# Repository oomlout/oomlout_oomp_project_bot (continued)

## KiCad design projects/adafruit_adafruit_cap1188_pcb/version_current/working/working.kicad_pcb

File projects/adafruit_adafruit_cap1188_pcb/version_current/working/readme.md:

# Adafruit-CAP1188-PCB by adafruit  
This is a harvested standardized copy of a project from github.  
The original project can be found at:  
https://github.com/adafruit/Adafruit-CAP1188-PCB  
Please consult that link for additional, details, files, and license information.  
Note: It was auto harvested and if the original repo had more than one board file or anything out of the ordinary the files here are likely not representative.

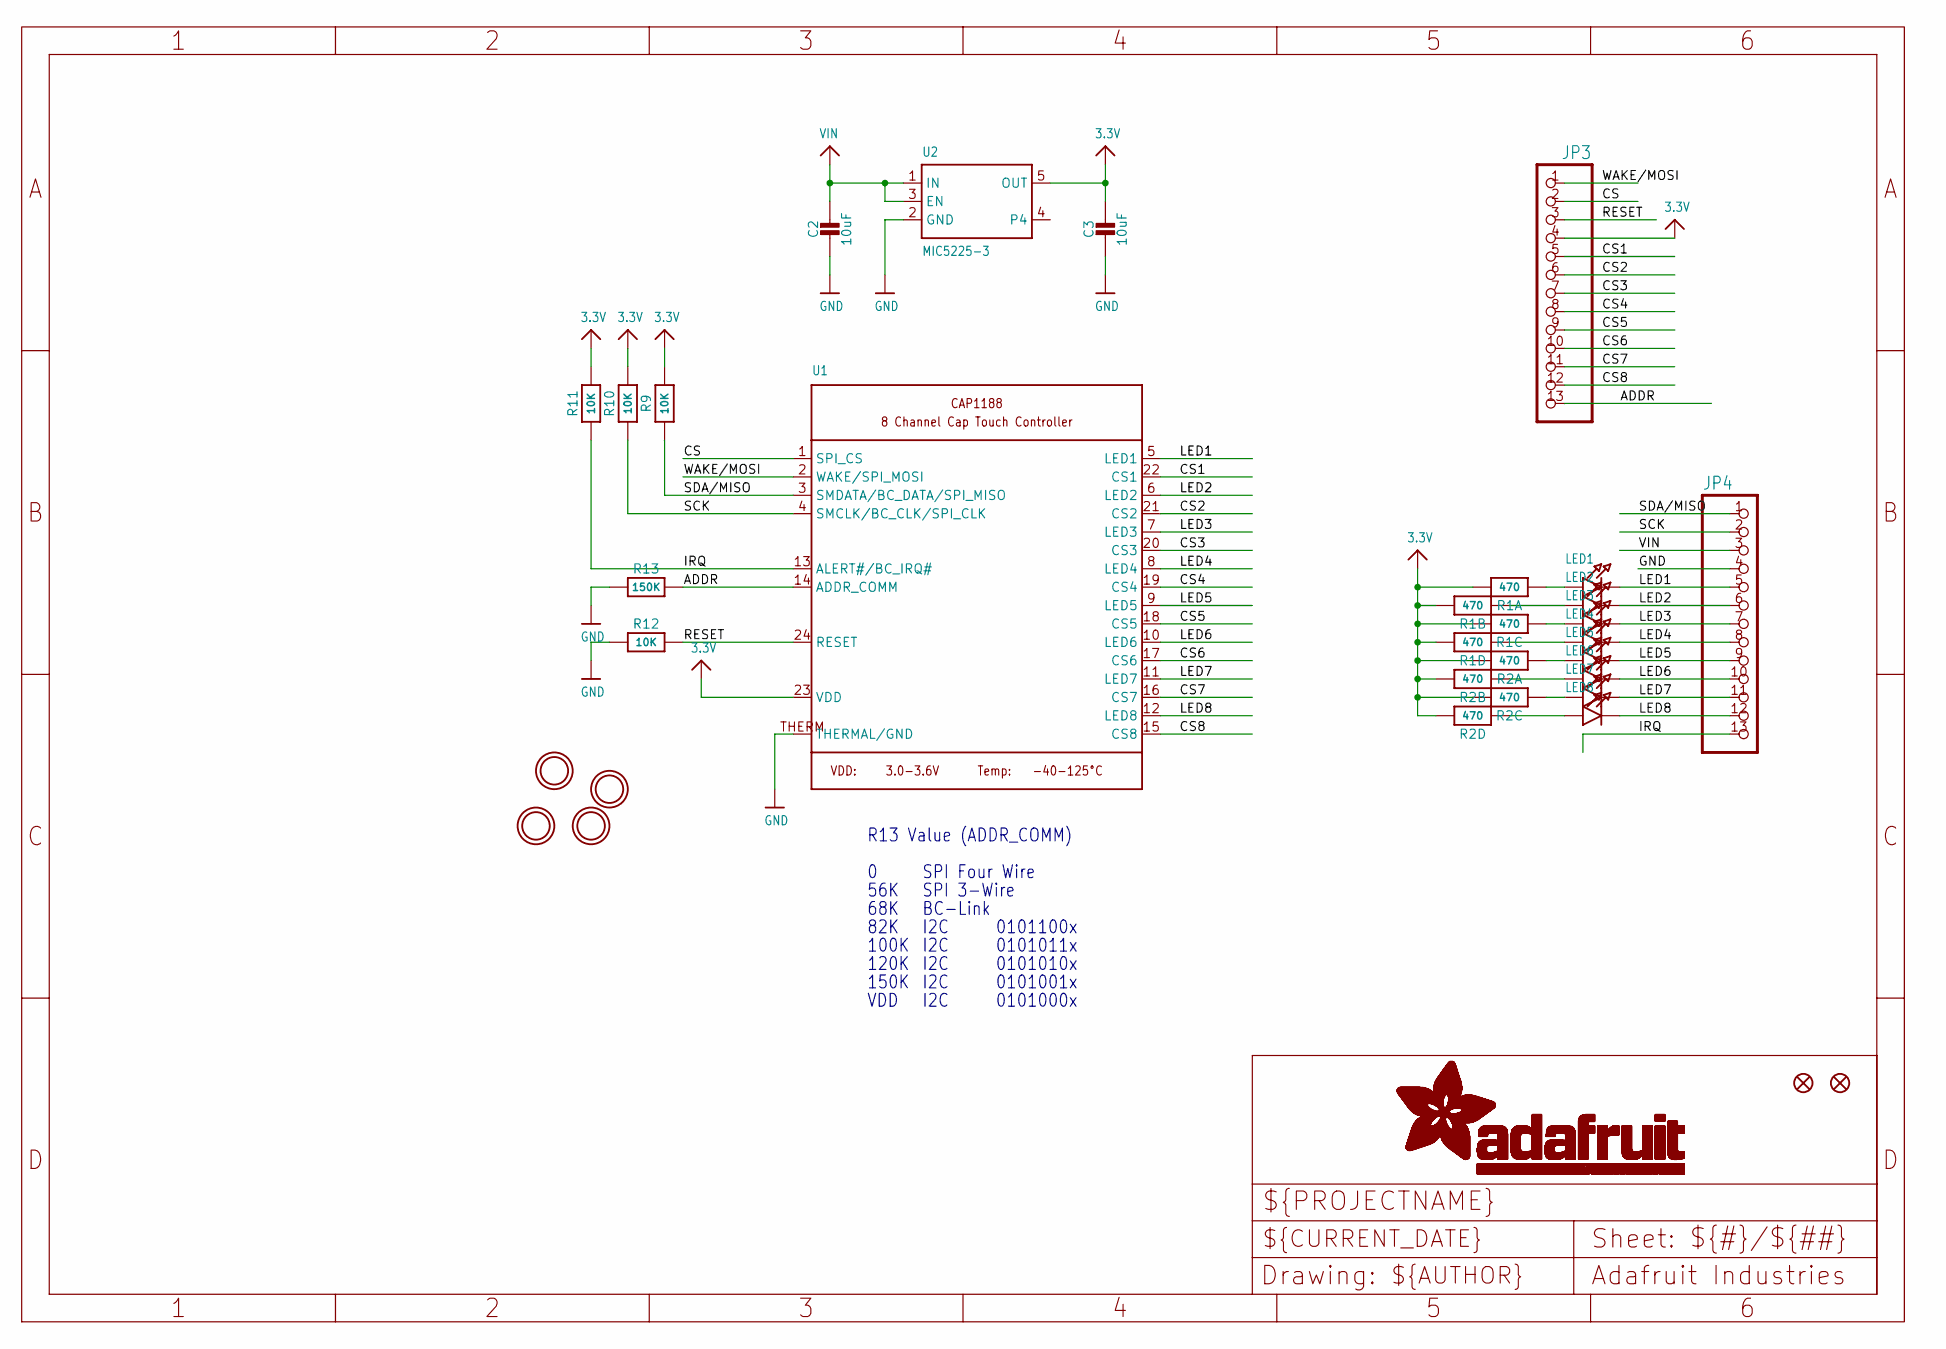
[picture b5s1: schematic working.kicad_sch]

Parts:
C2, C3: 10uF; 0805-NO
FID1, FID2: FIDUCIAL""; FIDUCIAL_1MM
JP3, JP4: HEADER-1X13; 1X13_ROUND_70
LED1, LED2, LED3, LED4, LED5, LED6, LED7, LED8: LED0805; CHIPLED_0805
R1, R2: 470; RESPACK_4X0603
R9, R10, R11, R12: 10K; 0805-NO
R13: 150K; _0805MP
U1: CAP1188; QFN24_4MM_SMSC
U2: MIC5225-3; SOT23-5
U$7, U$8, U$9, U$10: MOUNTINGHOLE2.0; MOUNTINGHOLE_2.0_PLATED

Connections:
3.3V: C3.1, JP3.4, R1.5 (2), R1.6 (2), R1.7 (2), R1.8 (2), R2.5 (2), R2.6 (2), R2.7 (2), R2.8 (2), R9.2, R10.2, R11.2, U1.23 (VDD), U2.5 (OUT)
ADDR: JP3.13, R13.2, U1.14 (ADDR_COMM)
CS: JP3.2, U1.1 (SPI_CS)
CS1: JP3.5, U1.22 (CS1)
CS2: JP3.6, U1.21 (CS2)
CS3: JP3.7, U1.20 (CS3)
CS4: JP3.8, U1.19 (CS4)
CS5: JP3.9, U1.18 (CS5)
CS6: JP3.10, U1.17 (CS6)
CS7: JP3.11, U1.16 (CS7)
CS8: JP3.12, U1.15 (CS8)
GND: C2.2, C3.2, JP4.4, R12.1, R13.1, U1.THERM (THERMAL/GND), U2.2 (GND)
IRQ: JP4.13, R11.1, U1.13 (ALERT#/BC_IRQ#)
LED1: JP4.5, LED1.C, U1.5 (LED1)
LED2: JP4.6, LED2.C, U1.6 (LED2)
LED3: JP4.7, LED3.C, U1.7 (LED3)
LED4: JP4.8, LED4.C, U1.8 (LED4)
LED5: JP4.9, LED5.C, U1.9 (LED5)
LED6: JP4.10, LED6.C, U1.10 (LED6)
LED7: JP4.11, LED7.C, U1.11 (LED7)
LED8: JP4.12, LED8.C, U1.12 (LED8)
unnamed: LED1.A, R1.1
unnamed: LED2.A, R1.2 (1)
unnamed: LED3.A, R1.3 (1)
unnamed: LED4.A, R1.4 (1)
unnamed: LED5.A, R2.1
unnamed: LED6.A, R2.2 (1)
unnamed: LED7.A, R2.3 (1)
unnamed: LED8.A, R2.4 (1)
RESET: JP3.3, R12.2, U1.24 (RESET)
SCK: JP4.2, R10.1, U1.4 (SMCLK/BC_CLK/SPI_CLK)
SDA/MISO: JP4.1, R9.1, U1.3 (SMDATA/BC_DATA/SPI_MISO)
VIN: C2.1, JP4.3, U2.1 (IN), U2.3 (EN)
WAKE/MOSI: JP3.1, U1.2 (WAKE/SPI_MOSI)

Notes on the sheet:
0101001x
68K
0101010x
150K
0101011x
VDD
I2C
0101000x
120K
0101100x
82K
56K
SPI 3-Wire
100K
R13 Value (ADDR_COMM)
SPI Four Wire
BC-Link

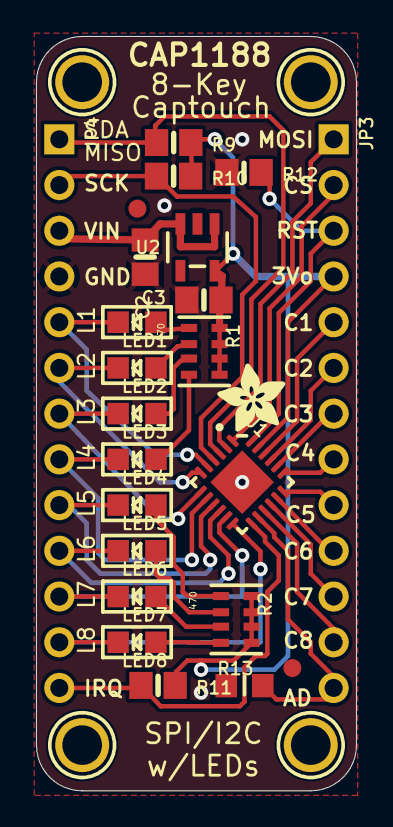
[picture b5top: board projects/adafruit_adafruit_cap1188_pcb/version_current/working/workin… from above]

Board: 2 copper layers, 17.8 x 41.9 mm, 29 parts (1 on the bottom side), 34 nets.

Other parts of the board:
U$13: ADAFRUIT_3.5MM
U$14: ADAFRUIT_9MM

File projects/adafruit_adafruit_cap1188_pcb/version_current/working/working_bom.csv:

Row,Description,Part,References,Value,Footprint,Quantity Per PCB,Status,Datasheet
1,,CAP_CERAMIC0805-NOOUTLINE,C2 C3,10uF,0805-NO,2, ,
2,,HEADER-1X13,JP3 JP4,HEADER-1X13,1X13_ROUND_70,2, ,
3,,LED0805,LED1 LED2 LED3 LED4 LED5 LED6 LED7 LED8,LED0805,CHIPLED_0805,8, ,
4,,RESISTOR_4PACK,R1 R2,470,RESPACK_4X0603,2, ,
5,,RESISTOR0805_NOOUTLINE,R9 R10 R11 R12,10K,0805-NO,4, ,
6,,RESISTOR_0805MP,R13,150K,_0805MP,1, ,
7,,CAP1188,U1,CAP1188,QFN24_4MM_SMSC,1, ,
8,,VREG_SOT23-5,U2,MIC5225-3,SOT23-5,1, ,





Project info:
Schematic:,working
Variant:,default
Revision:,
Date:,2023-08-02_17-08-32
KiCad Version:,7.0.6-7.0.6~ubuntu22.04.1
Statistics:
Component Groups:,8
Component Count:,21 (0 SMD/ 0 THT)
Fitted Components:,21 (0 SMD/ 0 THT)
Number of PCBs:,1
Total Components:,21

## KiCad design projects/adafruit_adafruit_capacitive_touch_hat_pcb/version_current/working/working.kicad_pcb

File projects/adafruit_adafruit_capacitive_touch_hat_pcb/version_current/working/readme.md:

# Adafruit-Capacitive-Touch-HAT-PCB by adafruit  
This is a harvested standardized copy of a project from github.  
The original project can be found at:  
https://github.com/adafruit/Adafruit-Capacitive-Touch-HAT-PCB  
Please consult that link for additional, details, files, and license information.  
Note: It was auto harvested and if the original repo had more than one board file or anything out of the ordinary the files here are likely not representative.

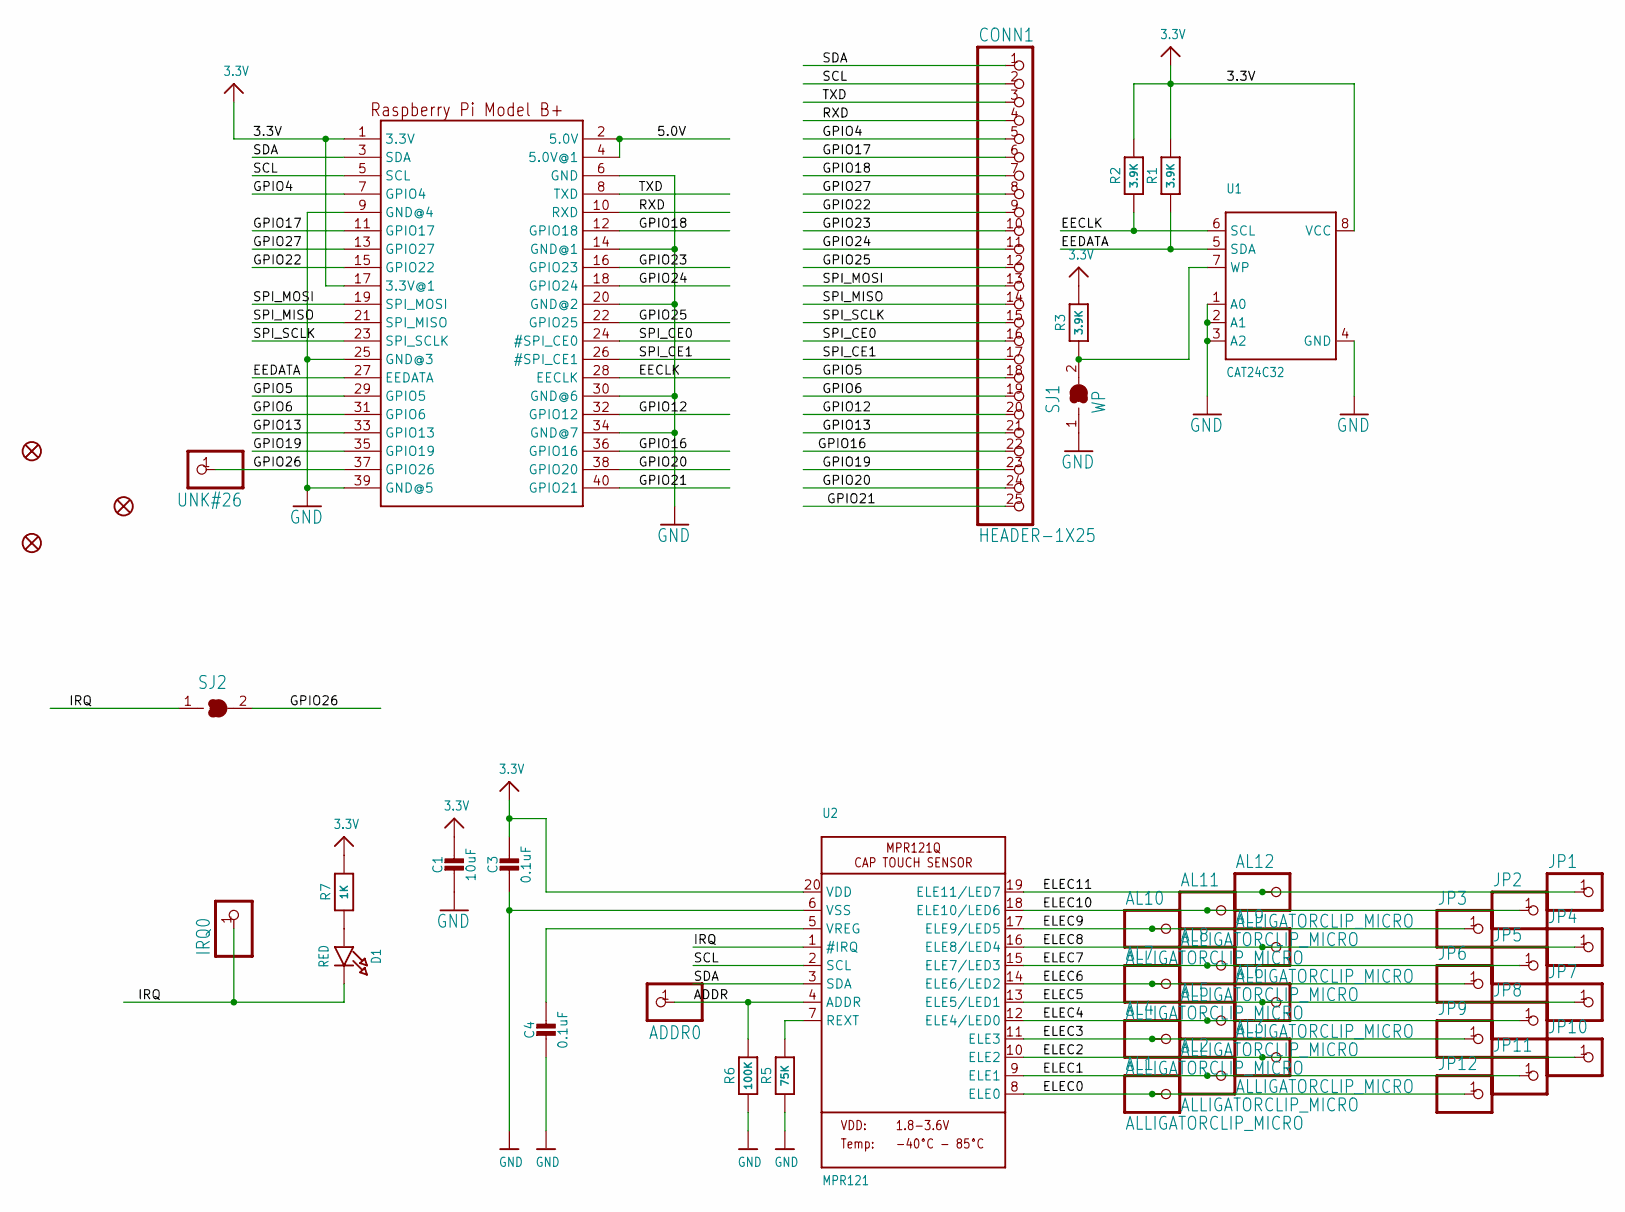
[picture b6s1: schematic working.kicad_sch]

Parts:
ADDR0: HEADER-1X1ROUND; 1X01_ROUND
AL1, AL2, AL3, AL4, AL5, AL6, AL7, AL8, AL9, AL10, AL11, AL12: ALLIGATORCLIP_MICRO; ALLIGATORCLIP
C1: 10uF; 0805-NO
C3, C4: 0.1uF; 0805-NO
CONN1: HEADER-1X25; 1X25_ROUND_70MIL
D1: RED; CHIPLED_0805_NOOUTLINE
FID1, FID2, FID3: FIDUCIAL""; FIDUCIAL_1MM
IRQ0: HEADER-1X1ROUND; 1X01_ROUND
JP1, JP2, JP3, JP4, JP5, JP6, JP7, JP8, JP9, JP10, JP11, JP12: HEADER-1X1ROUND; 1X01_ROUND
R1, R2, R3: 3.9K; 0805-NO
R5: 75K; 0805-NO
R6: 100K; 0805-NO
R7: 1K; 0805-NO
RPI1: RASPBERRYPI_BPLUS_HATSLOTS; PI_HAT_SLOTS
SJ1: WP; SOLDERJUMPER_CLOSEDWIRE
SJ2: SOLDERJUMPER_CLOSED; SOLDERJUMPER_CLOSEDWIRE
U1: CAT24C32; SOIC8_150MIL
U2: MPR121; QFN20_3MM_NOTHERMAL
UNK#26: HEADER-1X1ROUND; 1X01_ROUND

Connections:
3.3V: C1.1, C3.1, R1.2, R2.2, R3.2, R7.2, RPI1.1 (3.3V), RPI1.17 (3.3V@1), U1.8 (VCC), U2.20 (VDD)
5.0V: RPI1.2 (5.0V), RPI1.4 (5.0V@1)
ADDR: ADDR0.1, R6.2, U2.4 (ADDR)
EECLK: R2.1, RPI1.28 (EECLK), U1.6 (SCL)
EEDATA: R1.1, RPI1.27 (EEDATA), U1.5 (SDA)
ELEC0: AL1.P$1, AL1.P$2, JP12.1, U2.8 (ELE0)
ELEC1: AL2.P$1, AL2.P$2, JP11.1, U2.9 (ELE1)
ELEC2: AL3.P$1, AL3.P$2, JP10.1, U2.10 (ELE2)
ELEC3: AL4.P$1, AL4.P$2, JP9.1, U2.11 (ELE3)
ELEC4: AL5.P$1, AL5.P$2, JP8.1, U2.12 (ELE4/LED0)
ELEC5: AL6.P$1, AL6.P$2, JP7.1, U2.13 (ELE5/LED1)
ELEC6: AL7.P$1, AL7.P$2, JP6.1, U2.14 (ELE6/LED2)
ELEC7: AL8.P$1, AL8.P$2, JP5.1, U2.15 (ELE7/LED3)
ELEC8: AL9.P$1, AL9.P$2, JP4.1, U2.16 (ELE8/LED4)
ELEC9: AL10.P$1, AL10.P$2, JP3.1, U2.17 (ELE9/LED5)
ELEC10: AL11.P$1, AL11.P$2, JP2.1, U2.18 (ELE10/LED6)
ELEC11: AL12.P$1, AL12.P$2, JP1.1, U2.19 (ELE11/LED7)
GND: C1.2, C3.2, C4.2, R5.1, R6.1, RPI1.6 (GND), RPI1.9 (GND@4), RPI1.14 (GND@1), RPI1.20 (GND@2), RPI1.25 (GND@3), RPI1.30 (GND@6), RPI1.34 (GND@7), RPI1.39 (GND@5), SJ1.1, U1.1 (A0), U1.2 (A1), U1.3 (A2), U1.4 (GND), U2.6 (VSS)
GPIO4: CONN1.5, RPI1.7 (GPIO4)
GPIO5: CONN1.18, RPI1.29 (GPIO5)
GPIO6: CONN1.19, RPI1.31 (GPIO6)
GPIO12: CONN1.20, RPI1.32 (GPIO12)
GPIO13: CONN1.21, RPI1.33 (GPIO13)
GPIO16: CONN1.22, RPI1.36 (GPIO16)
GPIO17: CONN1.6, RPI1.11 (GPIO17)
GPIO18: CONN1.7, RPI1.12 (GPIO18)
GPIO19: CONN1.23, RPI1.35 (GPIO19)
GPIO20: CONN1.24, RPI1.38 (GPIO20)
GPIO21: CONN1.25, RPI1.40 (GPIO21)
GPIO22: CONN1.9, RPI1.15 (GPIO22)
GPIO23: CONN1.10, RPI1.16 (GPIO23)
GPIO24: CONN1.11, RPI1.18 (GPIO24)
GPIO25: CONN1.12, RPI1.22 (GPIO25)
GPIO26: RPI1.37 (GPIO26), SJ2.2, UNK#26.1
GPIO27: CONN1.8, RPI1.13 (GPIO27)
IRQ: D1.C, IRQ0.1, SJ2.1, U2.1 (#IRQ)
unnamed: R3.1, SJ1.2, U1.7 (WP)
unnamed: C4.1, U2.5 (VREG)
unnamed: R5.2, U2.7 (REXT)
unnamed: D1.A, R7.1
RXD: CONN1.4, RPI1.10 (RXD)
SCL: CONN1.2, RPI1.5 (SCL), U2.2 (SCL)
SDA: CONN1.1, RPI1.3 (SDA), U2.3 (SDA)
SPI_CE0: CONN1.16, RPI1.24 (#SPI_CE0)
SPI_CE1: CONN1.17, RPI1.26 (#SPI_CE1)
SPI_MISO: CONN1.14, RPI1.21 (SPI_MISO)
SPI_MOSI: CONN1.13, RPI1.19 (SPI_MOSI)
SPI_SCLK: CONN1.15, RPI1.23 (SPI_SCLK)
TXD: CONN1.3, RPI1.8 (TXD)

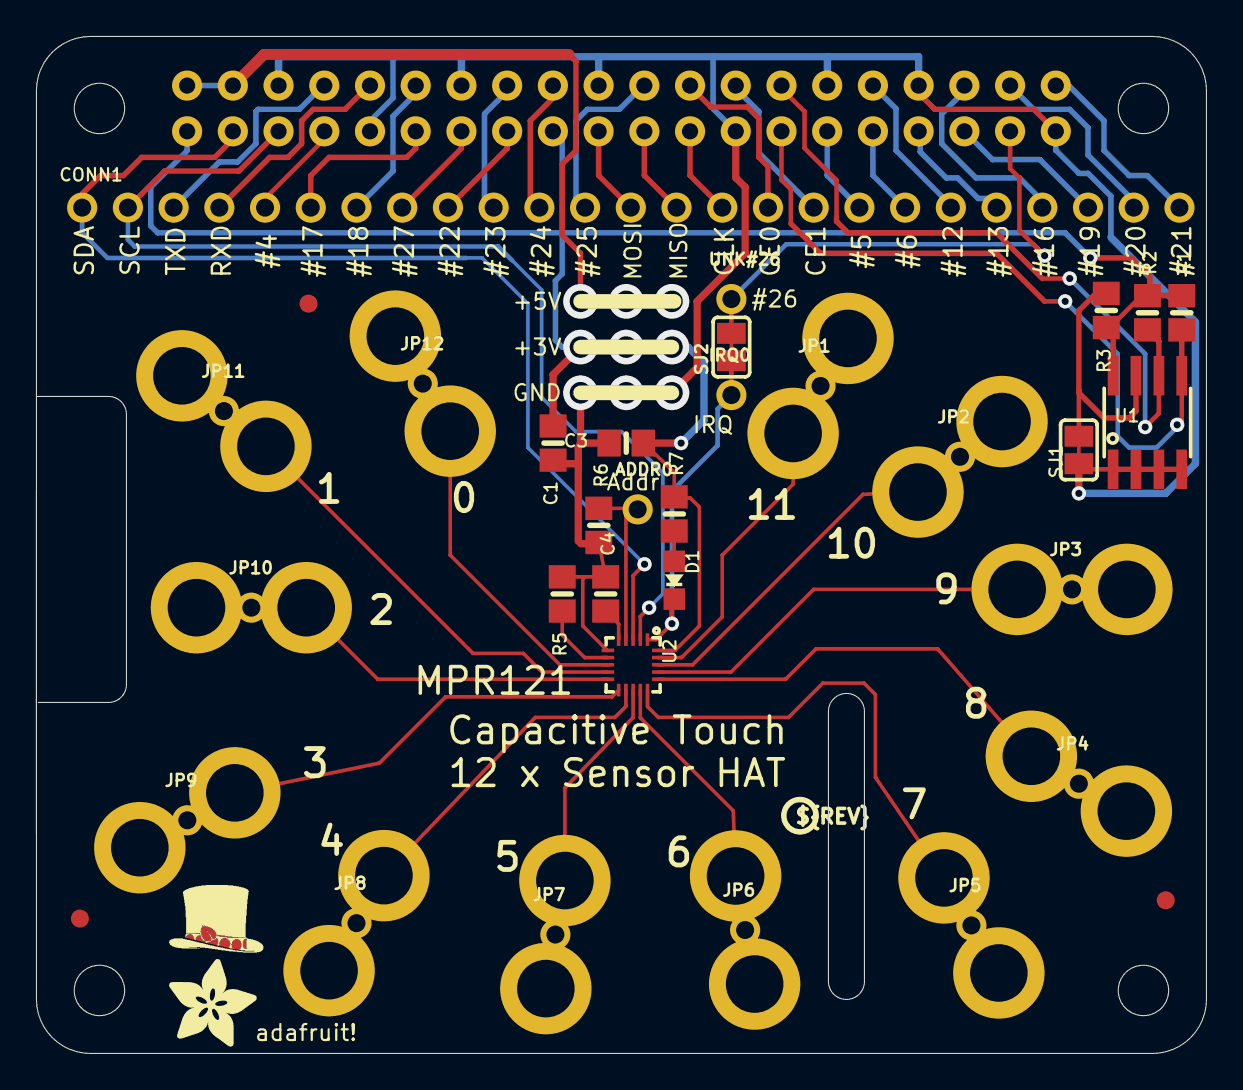
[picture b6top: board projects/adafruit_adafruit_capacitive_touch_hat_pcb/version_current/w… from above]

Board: 2 copper layers, 65.0 x 56.5 mm, 49 parts (0 on the bottom side), 49 nets.

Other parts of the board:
U$5: PIHATLOGO
U$6: PCBFEAT-REV-040
U$51: ADAFRUIT_5MM

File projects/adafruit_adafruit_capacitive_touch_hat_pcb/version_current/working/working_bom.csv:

Row,Description,Part,References,Value,Footprint,Quantity Per PCB,Status,Datasheet
1,,HEADER-1X1ROUND,ADDR0 IRQ0 JP1 JP2 JP3 JP4 JP5 JP6 JP7 JP8 JP9 JP10 JP11 JP12 UNK#26,HEADER-1X1ROUND,1X01_ROUND,15, ,
2,,ALLIGATORCLIP_MICRO,AL1 AL2 AL3 AL4 AL5 AL6 AL7 AL8 AL9 AL10 AL11 AL12,ALLIGATORCLIP_MICRO,ALLIGATORCLIP,12, ,
3,,CAP_CERAMIC0805-NOOUTLINE,C3 C4,0.1uF,0805-NO,2, ,
4,,CAP_CERAMIC0805-NOOUTLINE,C1,10uF,0805-NO,1, ,
5,,HEADER-1X25,CONN1,HEADER-1X25,1X25_ROUND_70MIL,1, ,
6,,LED0805_NOOUTLINE,D1,RED,CHIPLED_0805_NOOUTLINE,1, ,
7,,RESISTOR0805_NOOUTLINE,R7,1K,0805-NO,1, ,
8,,RESISTOR0805_NOOUTLINE,R1 R2 R3,3.9K,0805-NO,3, ,
9,,RESISTOR0805_NOOUTLINE,R5,75K,0805-NO,1, ,
10,,RESISTOR0805_NOOUTLINE,R6,100K,0805-NO,1, ,
11,,RASPBERRYPI_BPLUS_HATSLOTS,RPI1,RASPBERRYPI_BPLUS_HATSLOTS,PI_HAT_SLOTS,1, ,
12,,EEPROM_I2C_SOIC8_GENERIC,U1,CAT24C32,SOIC8_150MIL,1, ,
13,,MPR121Q,U2,MPR121,QFN20_3MM_NOTHERMAL,1, ,





Project info:
Schematic:,working
Variant:,default
Revision:,
Date:,2023-08-02_17-08-32
KiCad Version:,7.0.6-7.0.6~ubuntu22.04.1
Statistics:
Component Groups:,13
Component Count:,41 (0 SMD/ 0 THT)
Fitted Components:,41 (0 SMD/ 0 THT)
Number of PCBs:,1
Total Components:,41

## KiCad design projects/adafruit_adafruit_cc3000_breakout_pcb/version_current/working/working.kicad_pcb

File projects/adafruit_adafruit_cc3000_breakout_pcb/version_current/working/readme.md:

# OOMP Project  
## Adafruit-CC3000-Breakout-PCB  by adafruit  
  
oomp key: oomp_projects_flat_adafruit_adafruit_cc3000_breakout_pcb  
(snippet of original readme)  
  
- Adafruit CC3000 Breakout PCB  

This is the PCB for the Adafruit CC3000 WiFi Breakout  
Format is EagleCAD schematic and board layout  
  
For more details, check out the product page at  
  
* http://www.adafruit.com/products/1510  
* http://www.adafruit.com/products/1469  
  
For years we've seen all sorts of microcontroller-friendly WiFi modules but none of them were really Adafruit-worthy. Either they were too slow, or too difficult to use, or required signing an NDA, or had limited functionality, or too expensive, or too large. So we shied away from carrying any general purpose microcontroller-friendly WiFi boards.  
  
NO LONGER! The CC3000 hits that sweet spot of usability, price and capability. It uses SPI for communication (not UART!) so you can push data as fast as you want or as slow as you want. It has a proper interrupt system with IRQ pin so you can have asynchronous connections. It supports 802.11b/g, open/WEP/WPA/WPA2 security, TKIP & AES. A built in TCP/IP stack with a "BSD socket" interface. TCP and UDP in both client and server mode, up to 4 concurrent sockets. It does not support "AP" mode, it can connect to an access point but it cannot be an access point.  
  
Please note that the CC3000 module is being phased out and [we suggest the WINC1500 as a replacement - it has SSL support, soft-AP capability, and is more reliable.](https://www.adafruit.com/products/2999).  
  
We wrapped  
  full source readme at [readme_src.md](readme_src.md)  
  
source repo at: [https://github.com/adafruit/Adafruit-CC3000-Breakout-PCB](https://github.com/adafruit/Adafruit-CC3000-Breakout-PCB)  
## Board  

## Schematic  

[schematic pdf](working_schematic.pdf)  
## Images

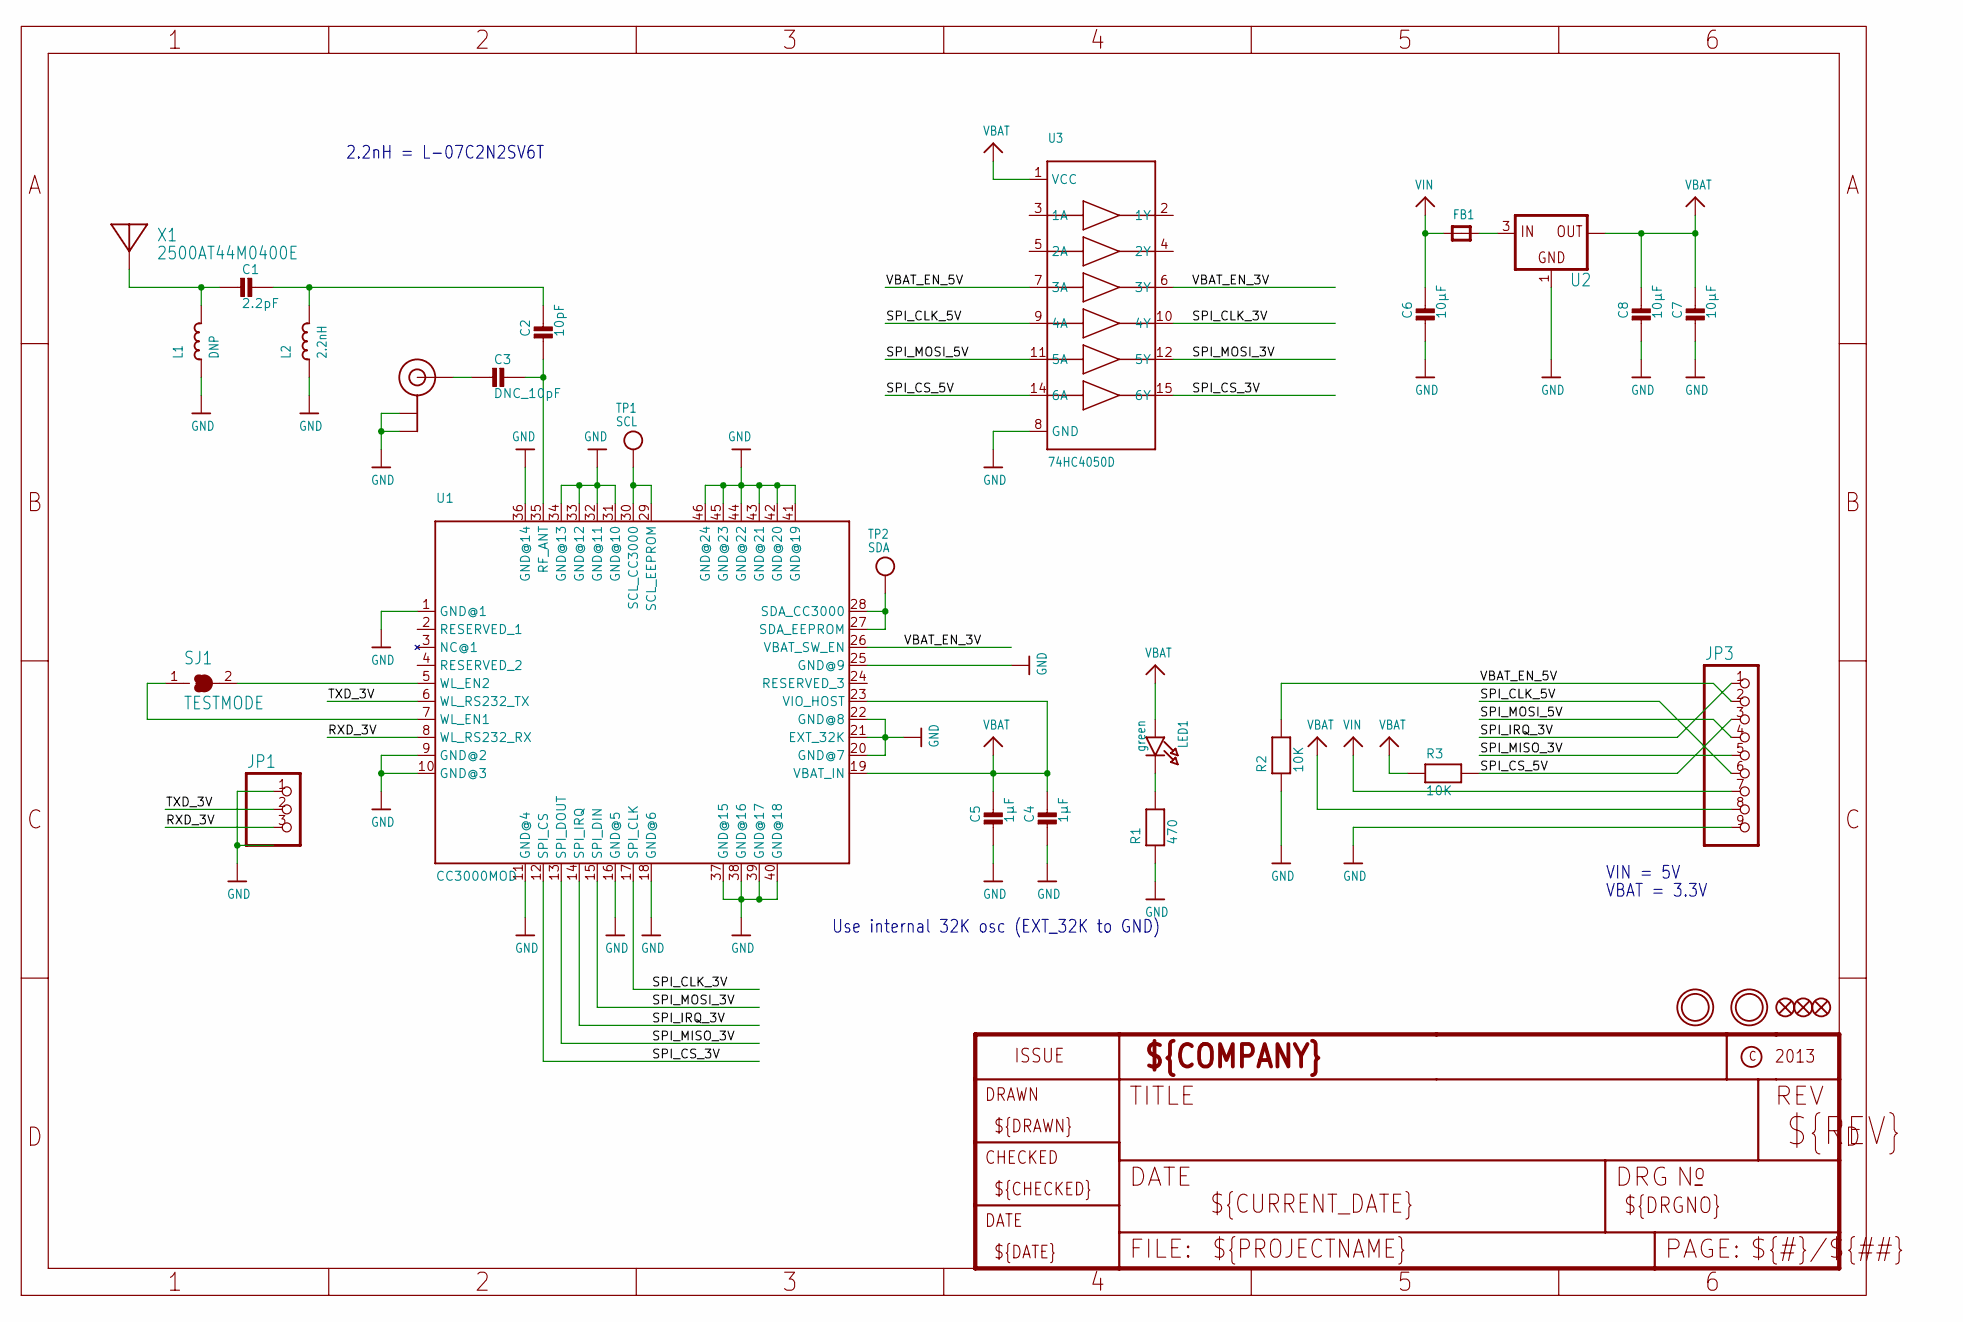
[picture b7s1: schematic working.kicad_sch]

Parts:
C1: 2.2pF; _0402
C2: 10pF; _0402
C3: DNC_10pF; _0402
C4, C5: 1µF; _0805MP
C6, C7, C8: 10µF; _0805MP
FB1: FERRITE_0805MP; _0805MP
FID1, FID2, FID3: FIDUCIAL""; FIDUCIAL_1MM
JP1: HEADER-1X3ROUND; 1X03_ROUND
JP3: HEADER-1X970MIL; 1X09_ROUND_70
L1: DNP; _0402
L2: 2.2nH; _0402
LED1: green; CHIPLED_0805_NOOUTLINE
R1: 470; 0805-NO
R2, R3: 10K; _0805MP
SJ1: TESTMODE; SOLDERJUMPER_CLOSEDWIRE
TP1: SCL; TESTPOINT_PAD_1MM
TP2: SDA; TESTPOINT_PAD_1MM
U1: CC3000MOD
U2: VREG_SOT223; SOT223-R
U3: 74HC4050D; SOIC16
U$24, U$34: MOUNTINGHOLE2.5; MOUNTINGHOLE_2.5_PLATED
U$35: U.FL
X1: 2500AT44M0400E; ANT_2500AT44M0400

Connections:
GND: C4.2, C5.2, C6.2, C7.2, C8.2, JP1.1, JP3.9, L1.1, L2.1, R1.1, R2.1, U1.1 (GND@1), U1.9 (GND@2), U1.10 (GND@3), U1.11 (GND@4), U1.16 (GND@5), U1.18 (GND@6), U1.20 (GND@7), U1.21 (EXT_32K), U1.22 (GND@8), U1.25 (GND@9), U1.31 (GND@10), U1.32 (GND@11), U1.33 (GND@12), U1.34 (GND@13), U1.36 (GND@14), U1.37 (GND@15), U1.38 (GND@16), U1.39 (GND@17), U1.40 (GND@18), U1.41 (GND@19), U1.42 (GND@20), U1.43 (GND@21), U1.44 (GND@22), U1.45 (GND@23), U1.46 (GND@24), U2.1 (GND), U3.8 (GND), U$35.P$1 (GND@0), U$35.P$2 (GND@1)
unnamed: C1.2, L1.2, X1.FEED
unnamed: C1.1, C2.1, L2.2
unnamed: C3.2, U$35.P$3 (SIGNAL)
unnamed: C2.2, C3.1, U1.35 (RF_ANT)
unnamed: SJ1.2, U1.5 (WL_EN2)
unnamed: SJ1.1, U1.7 (WL_EN1)
unnamed: LED1.C, R1.2
unnamed: FB1.2, U2.3 (IN)
RXD_3V: JP1.3, U1.8 (WL_RS232_RX)
SCL_3V: TP1.P$1, U1.29 (SCL_EEPROM), U1.30 (SCL_CC3000)
SDA_3V: TP2.P$1, U1.27 (SDA_EEPROM), U1.28 (SDA_CC3000)
SPI_CLK_3V: U1.17 (SPI_CLK), U3.10 (4Y)
SPI_CLK_5V: JP3.6, U3.9 (4A)
SPI_CS_3V: U1.12 (SPI_CS), U3.15 (6Y)
SPI_CS_5V: JP3.3, R3.2, U3.14 (6A)
SPI_IRQ_3V: JP3.1, U1.14 (SPI_IRQ)
SPI_MISO_3V: JP3.5, U1.13 (SPI_DOUT)
SPI_MOSI_3V: U1.15 (SPI_DIN), U3.12 (5Y)
SPI_MOSI_5V: JP3.4, U3.11 (5A)
TXD_3V: JP1.2, U1.6 (WL_RS232_TX)
VBAT: C4.1, C5.1, C7.1, C8.1, JP3.8, LED1.A, R3.1, U1.19 (VBAT_IN), U1.23 (VIO_HOST), U2.2 (OUT), U2.4 (OUT), U3.1 (VCC)
VBAT_EN_3V: U1.26 (VBAT_SW_EN), U3.6 (3Y)
VBAT_EN_5V: JP3.2, R2.2, U3.7 (3A)
VIN: C6.1, FB1.1, JP3.7

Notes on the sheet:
VIN = 5V
VBAT = 3.3V
2.2nH = L-07C2N2SV6T
Use internal 32K osc (EXT_32K to GND)

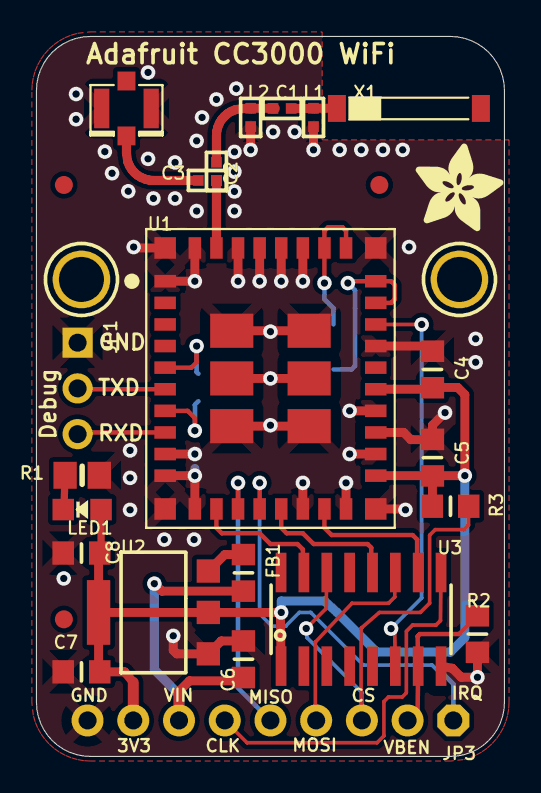
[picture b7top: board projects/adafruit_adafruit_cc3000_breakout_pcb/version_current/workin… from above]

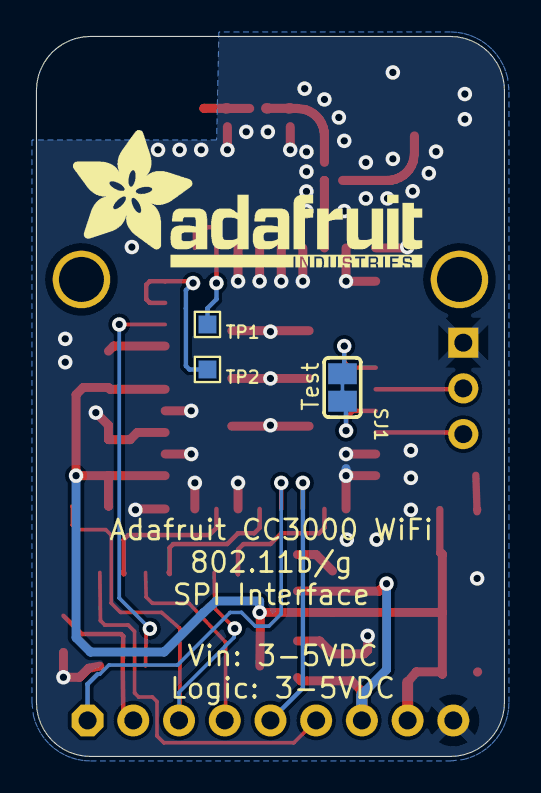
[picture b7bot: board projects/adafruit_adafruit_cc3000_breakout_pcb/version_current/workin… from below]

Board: 2 copper layers, 26.0 x 40.0 mm, 32 parts (4 on the bottom side), 25 nets.

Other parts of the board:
U$8: ADAFRUIT_5MM
U$36: ADAFRUIT_TEXT_20MM

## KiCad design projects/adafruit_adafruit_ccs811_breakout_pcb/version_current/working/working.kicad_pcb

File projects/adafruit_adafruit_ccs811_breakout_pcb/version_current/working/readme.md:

# OOMP Project  
## Adafruit-CCS811-Breakout-PCB  by adafruit  
  
oomp key: oomp_projects_flat_adafruit_adafruit_ccs811_breakout_pcb  
(snippet of original readme)  
  
-- Adafruit CCS811 Breakout PCB  
  
<a href="http://www.adafruit.com/products/3566"><br/>  
<a href="http://www.adafruit.com/products/3566"><br/>  
Click here to purchase one from the Adafruit shop</a>  
  
PCB files for the Adafruit CCS811 air quality sensor breakout board. Format is EagleCAD schematic and board layout  
  
For more details, check out the product page at  
* https://www.adafruit.com/products/3566  
  
--- Description  
  
Breathe easy - we finally have an I2C VOC/eCO2 sensor in the Adafruit shop! Add air quality monitoring to your project and with an Adafruit CCS811 Air Quality Sensor Breakout. This sensor from AMS is a gas sensor that can detect a wide range of Volatile Organic Compounds (VOCs) and is intended for indoor air quality monitoring. When connected to your microcontroller (running our library code) it will return a Total Volatile Organic Compound (TVOC) reading and an equivalent carbon dioxide reading (eCO2) over I2C. There is also an onboard thermistor that can be used to calculate the local ambient temperature.  
  
The CCS811 has a 'standard' hot-plate MOX sensor, as well as a small microcontroller that controls power to the plate, reads the analog voltage, and provides an I2C interface to read from.  
  
This part will measure eCO2 (equivalent calculated carbon-dioxide) concentration within a range of 400 to 8192 parts per million (ppm), and TVOC (Total Volatile Organic Compo  
  full source readme at [readme_src.md](readme_src.md)  
  
source repo at: [https://github.com/adafruit/Adafruit-CCS811-Breakout-PCB](https://github.com/adafruit/Adafruit-CCS811-Breakout-PCB)  
## Board  

## Schematic  

[schematic pdf](working_schematic.pdf)  
## Images

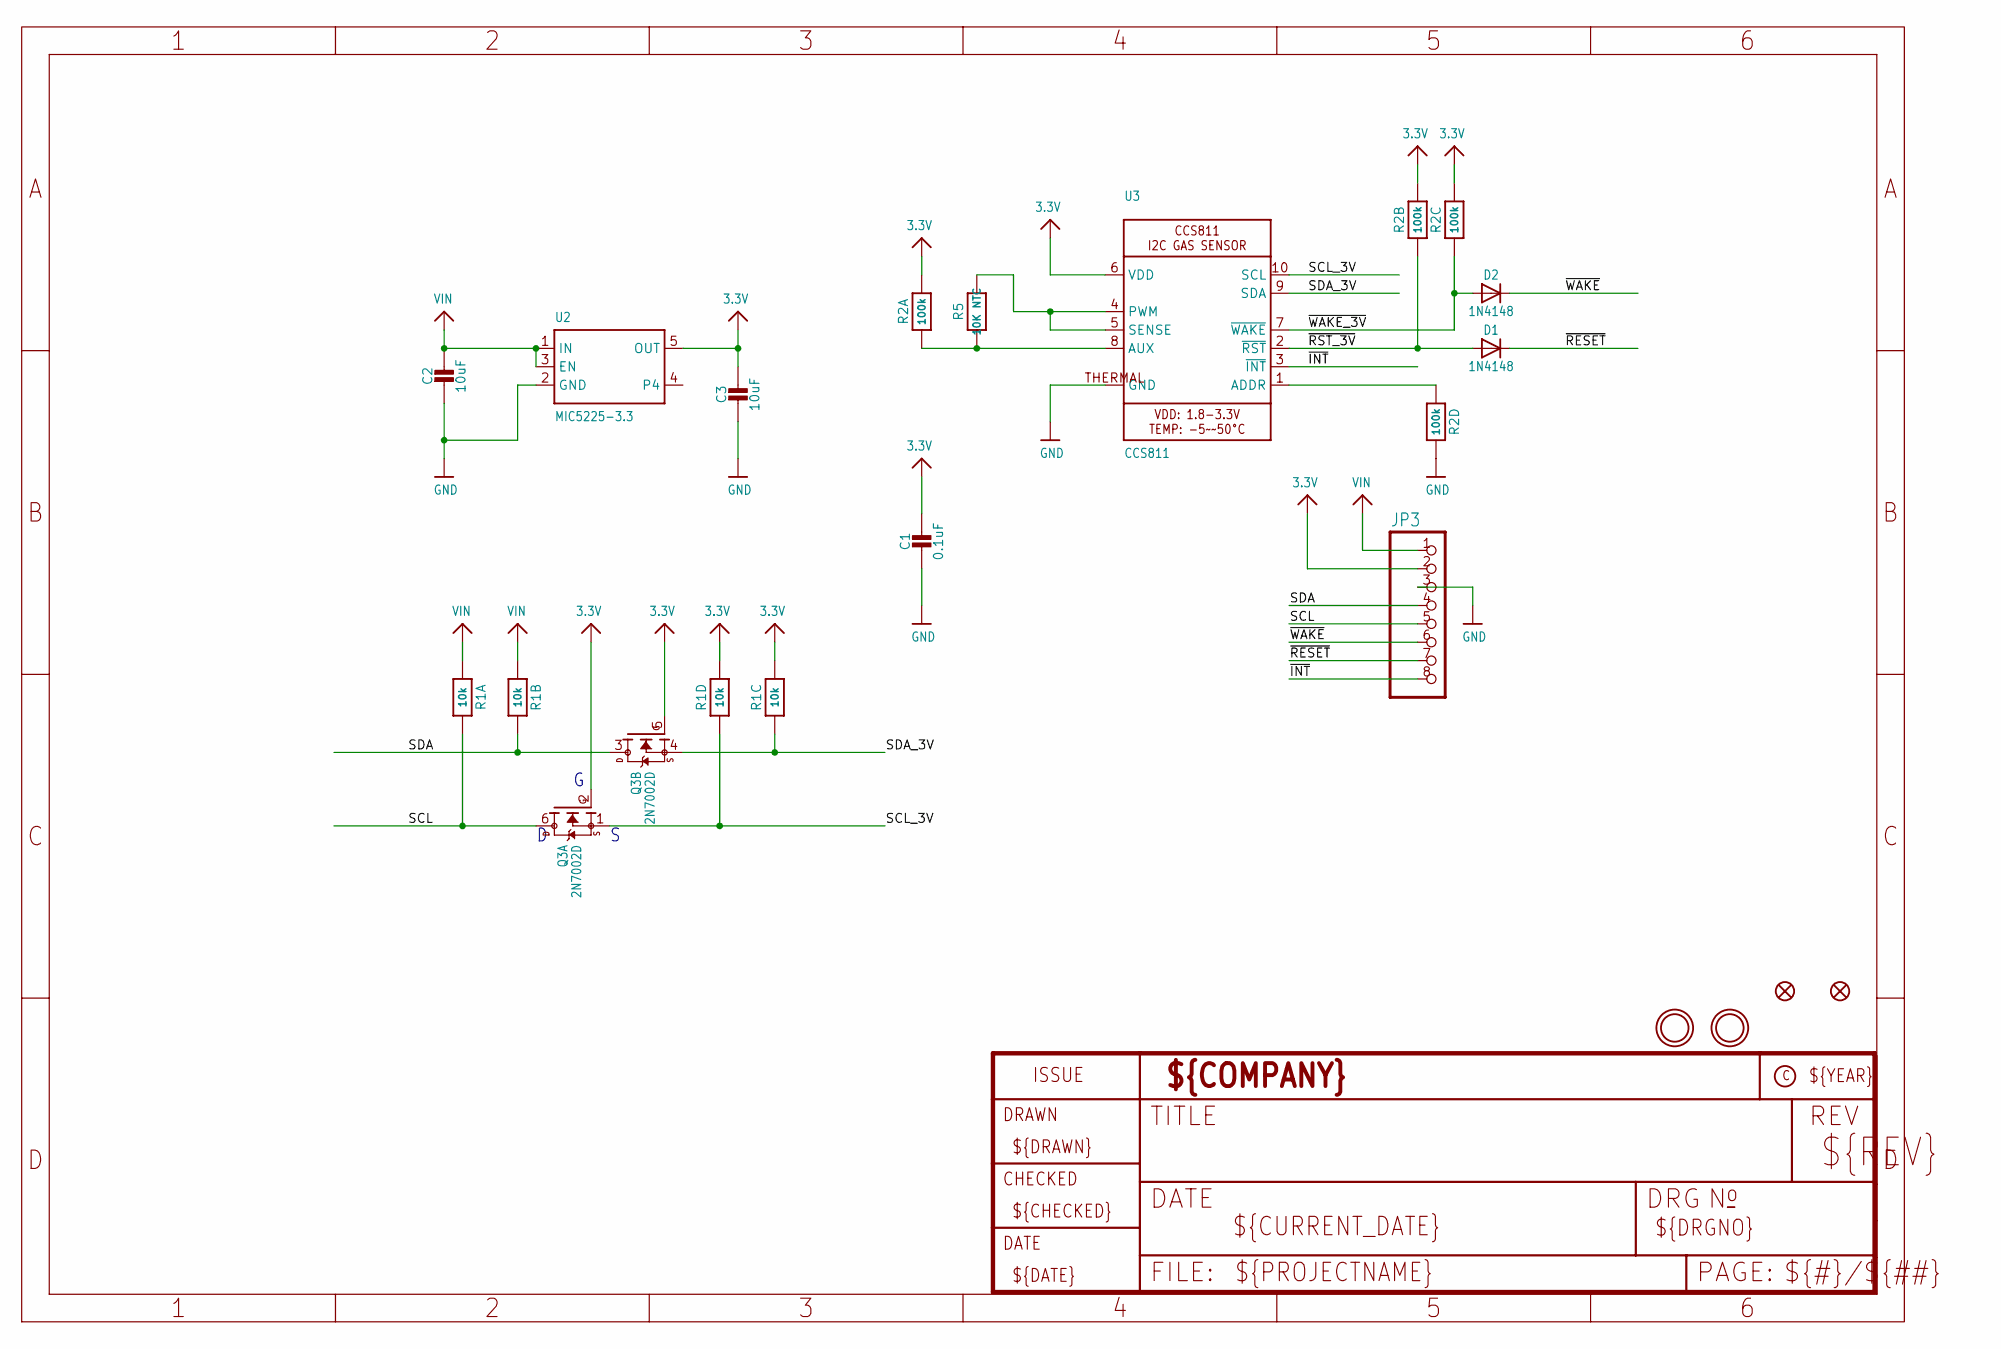
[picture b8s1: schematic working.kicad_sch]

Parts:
C1: 0.1uF; 0603-NO
C2, C3: 10uF; 0805-NO
D1, D2: 1N4148; SOD-323
FID1, FID2: FIDUCIAL_1MM
JP3: HEADER-1X870MIL; 1X08_ROUND_70
Q3: 2N7002D; SOT363
R1: 10k; RESPACK_4X0603
R2: 100k; RESPACK_4X0603
R5: 10K NTC; _0402
U2: MIC5225-3.3; SOT23-5
U3: CCS811
U$3, U$4: MOUNTINGHOLE2.5; MOUNTINGHOLE_2.5_PLATED

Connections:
3.3V: C1.1, C3.1, JP3.2, Q3.2 (G), Q3.5 (G), R1.3 (1), R1.4 (1), R2.6 (2), R2.7 (2), R2.8 (2), U2.5 (OUT), U3.6 (VDD)
GND: C1.2, C2.2, C3.2, JP3.3, R2.5 (2), U2.2 (GND), U3.THERMAL (GND)
unnamed: R5.2, U3.4 (PWM), U3.5 (SENSE)
unnamed: R2.1, R5.1, U3.8 (AUX)
unnamed: R2.4 (1), U3.1 (ADDR)
SCL: JP3.5, Q3.6 (D), R1.8 (2)
SCL_3V: Q3.1 (S), R1.5 (2), U3.10 (SCL)
SDA: JP3.4, Q3.3 (D), R1.7 (2)
SDA_3V: Q3.4 (S), R1.6 (2), U3.9 (SDA)
VIN: C2.1, JP3.1, R1.1, R1.2 (1), U2.1 (IN), U2.3 (EN)
~INT: JP3.8, U3.3 (~INT)
~RESET: D1.C, JP3.7
~RST_3V: D1.A, R2.2 (1), U3.2 (~RST)
~WAKE_3V: D2.A, R2.3 (1), U3.7 (~WAKE)
~WAKE: D2.C, JP3.6

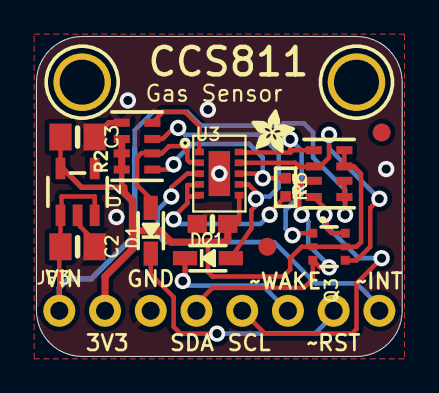
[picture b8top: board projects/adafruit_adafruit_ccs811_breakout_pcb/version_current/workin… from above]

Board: 2 copper layers, 20.3 x 17.8 mm, 18 parts (1 on the bottom side), 15 nets.

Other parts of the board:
U$1: ADAFRUIT_3.5MM
U$8: ADAFRUIT_2.5MM
